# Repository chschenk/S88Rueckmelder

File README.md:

# S88Rueckmelder
S88 Rückmelder Modul zum Anschluss von Rückmeldern an eine S88N Zentrale

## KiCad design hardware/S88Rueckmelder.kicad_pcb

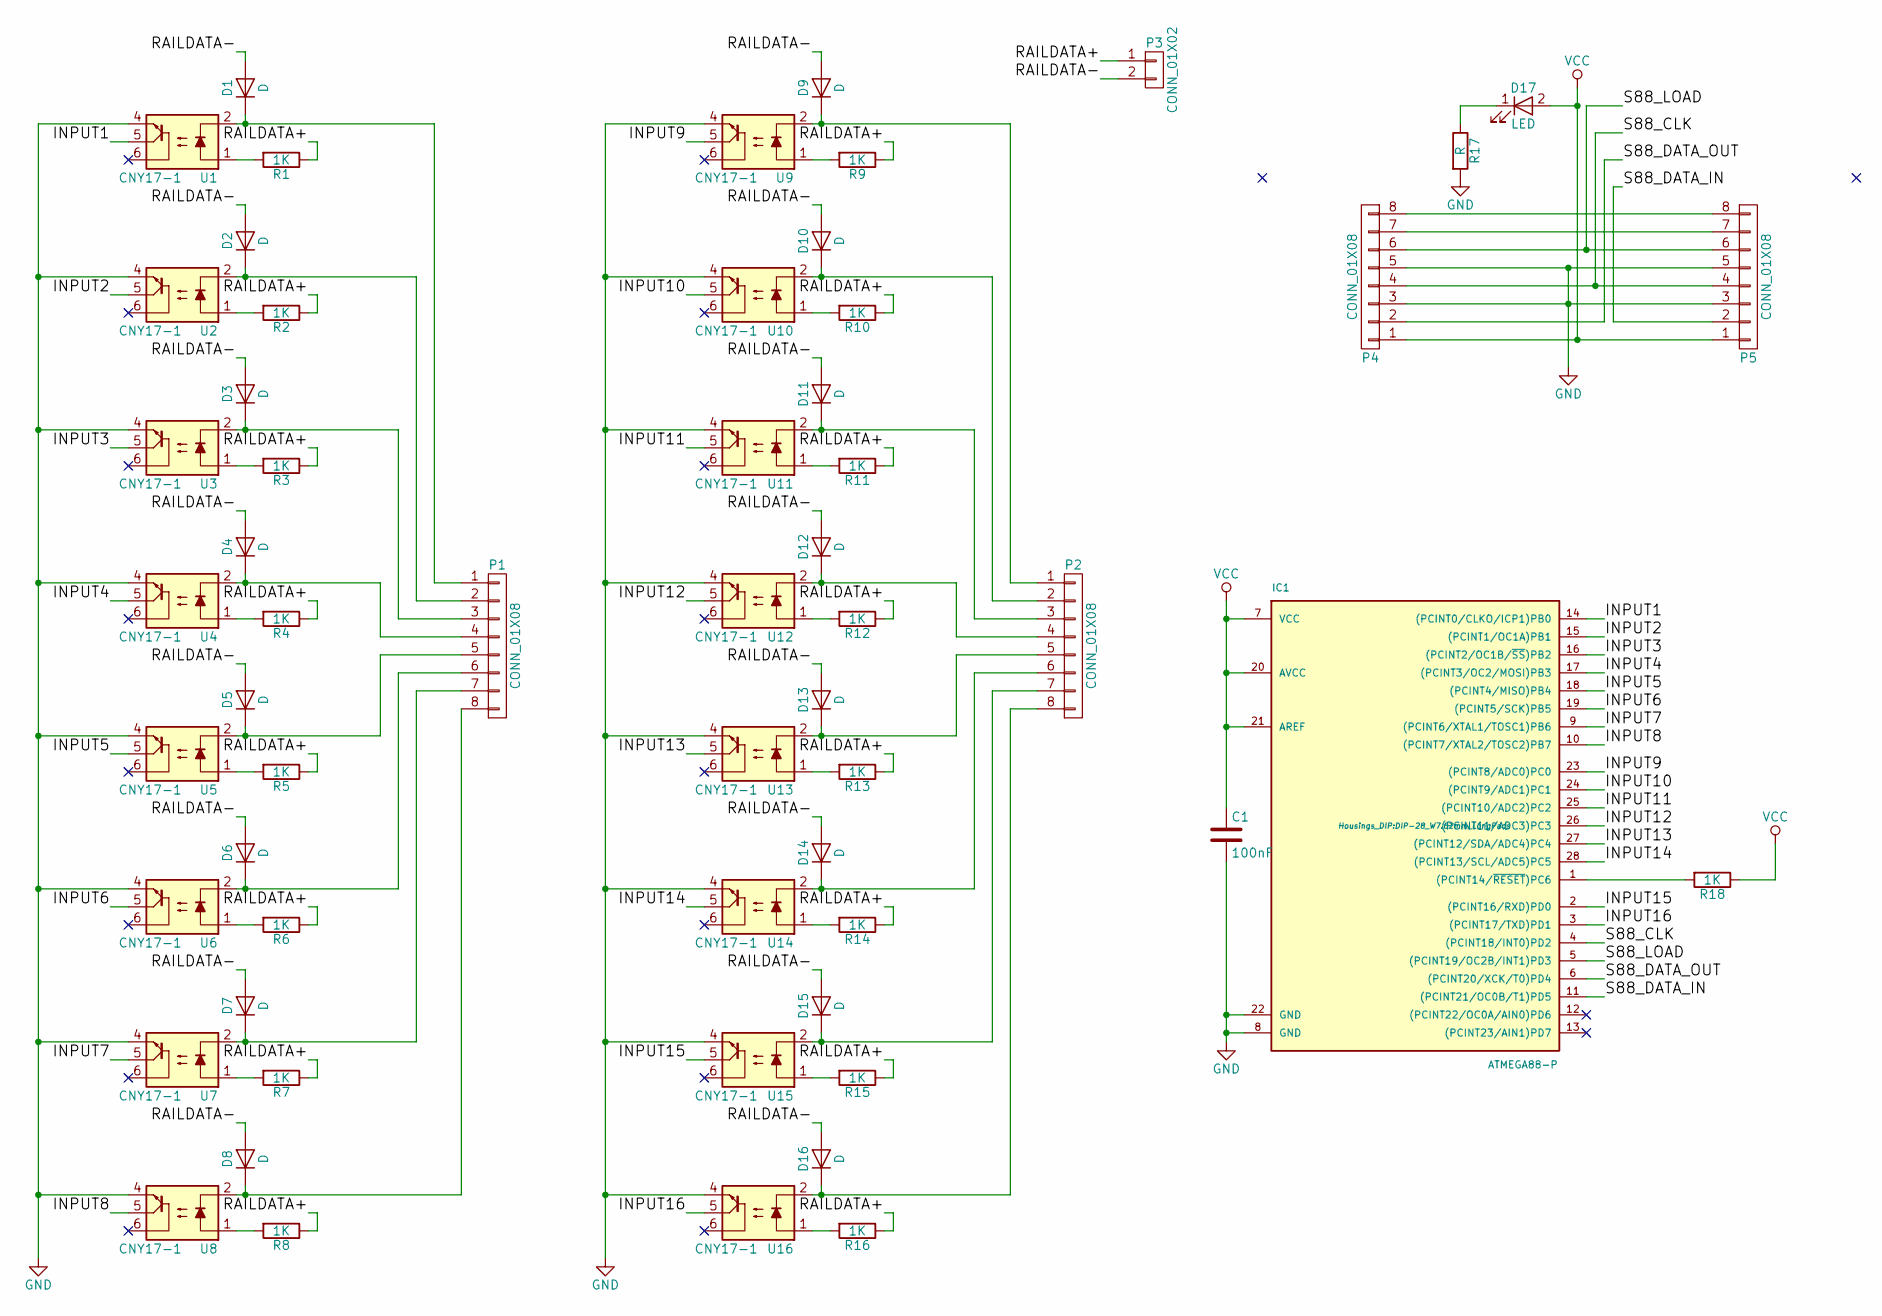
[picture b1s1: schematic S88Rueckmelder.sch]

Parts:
C1: 100nF; C_Disc_D5.1mm_W3.2mm_P5.00mm
D1, D2, D3, D4, D5, D6, D7, D8, D9, D10, D11, D12, D13, D14, D15, D16: D; D_DO-35_SOD27_P7.62mm_Horizontal
D17: LED; LED_D5.0mm
IC1: ATMEGA88-P; DIP-28_W7.62mm_LongPads
P1, P2: CONN_01X08; TerminalBlock_Phoenix_MKDS1.5-8pol
P3: CONN_01X02; AK300-2
P4, P5: CONN_01X08; RJ45_8
R1, R2, R3, R4, R5, R6, R7, R8, R9, R10, R11, R12, R13, R14, R15, R16: 1K; R_Axial_DIN0207_L6.3mm_D2.5mm_P7.62mm_Horizontal
R17: R; R_Axial_DIN0207_L6.3mm_D2.5mm_P10.16mm_Horizontal
R18: 1K; R_Axial_DIN0207_L6.3mm_D2.5mm_P10.16mm_Horizontal
U1, U2, U3, U4, U5, U6, U7, U8, U9, U10, U11, U12, U13, U14, U15, U16: CNY17-1; DIP-6_W7.62mm_LongPads

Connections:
/INPUT1: IC1.14 ((PCINT0/CLKO/ICP1)PB0), U1.5
/INPUT2: IC1.15 ((PCINT1/OC1A)PB1), U2.5
/INPUT3: IC1.16 ((PCINT2/OC1B/~SS~)PB2), U3.5
/INPUT4: IC1.17 ((PCINT3/OC2/MOSI)PB3), U4.5
/INPUT5: IC1.18 ((PCINT4/MISO)PB4), U5.5
/INPUT6: IC1.19 ((PCINT5/SCK)PB5), U6.5
/INPUT7: IC1.9 ((PCINT6/XTAL1/TOSC1)PB6), U7.5
/INPUT8: IC1.10 ((PCINT7/XTAL2/TOSC2)PB7), U8.5
/INPUT9: IC1.23 ((PCINT8/ADC0)PC0), U9.5
/INPUT10: IC1.24 ((PCINT9/ADC1)PC1), U10.5
/INPUT11: IC1.25 ((PCINT10/ADC2)PC2), U11.5
/INPUT12: IC1.26 ((PCINT11/ADC3)PC3), U12.5
/INPUT13: IC1.27 ((PCINT12/SDA/ADC4)PC4), U13.5
/INPUT14: IC1.28 ((PCINT13/SCL/ADC5)PC5), U14.5
/INPUT15: IC1.2 ((PCINT16/RXD)PD0), U15.5
/INPUT16: IC1.3 ((PCINT17/TXD)PD1), U16.5
/RAILDATA+: P3.1, R1.1, R2.1, R3.1, R4.1, R5.1, R6.1, R7.1, R8.1, R9.1, R10.1, R11.1, R12.1, R13.1, R14.1, R15.1, R16.1
/RAILDATA-: D1.2 (A), D2.2 (A), D3.2 (A), D4.2 (A), D5.2 (A), D6.2 (A), D7.2 (A), D8.2 (A), D9.2 (A), D10.2 (A), D11.2 (A), D12.2 (A), D13.2 (A), D14.2 (A), D15.2 (A), D16.2 (A), P3.2
/S88_CLK: IC1.4 ((PCINT18/INT0)PD2), P4.4, P5.4
/S88_DATA_IN: IC1.11 ((PCINT21/OC0B/T1)PD5), P5.2
/S88_DATA_OUT: IC1.6 ((PCINT20/XCK/T0)PD4), P4.2
/S88_LOAD: IC1.5 ((PCINT19/OC2B/INT1)PD3), P4.6, P5.6
GND: C1.2, IC1.8 (GND), IC1.22 (GND), P4.3, P4.5, P5.3, P5.5, R17.2, U1.4, U2.4, U3.4, U4.4, U5.4, U6.4, U7.4, U8.4, U9.4, U10.4, U11.4, U12.4, U13.4, U14.4, U15.4, U16.4
unnamed: D1.1 (K), P1.1, U1.2
unnamed: D2.1 (K), P1.2, U2.2
unnamed: D3.1 (K), P1.3, U3.2
unnamed: D4.1 (K), P1.4, U4.2
unnamed: D5.1 (K), P1.5, U5.2
unnamed: D6.1 (K), P1.6, U6.2
unnamed: D7.1 (K), P1.7, U7.2
unnamed: D8.1 (K), P1.8, U8.2
unnamed: D9.1 (K), P2.1, U9.2
unnamed: D10.1 (K), P2.2, U10.2
unnamed: D11.1 (K), P2.3, U11.2
unnamed: D12.1 (K), P2.4, U12.2
unnamed: D13.1 (K), P2.5, U13.2
unnamed: D14.1 (K), P2.6, U14.2
unnamed: D15.1 (K), P2.7, U15.2
unnamed: D16.1 (K), P2.8, U16.2
unnamed: D17.1 (K), R17.1
unnamed: IC1.1 ((PCINT14/~RESET~)PC6), R18.2
unnamed: P4.7, P5.7
unnamed: P4.8, P5.8
unnamed: R1.2, U1.1
unnamed: R2.2, U2.1
unnamed: R3.2, U3.1
unnamed: R4.2, U4.1
unnamed: R5.2, U5.1
unnamed: R6.2, U6.1
unnamed: R7.2, U7.1
unnamed: R8.2, U8.1
unnamed: R9.2, U9.1
unnamed: R10.2, U10.1
unnamed: R11.2, U11.1
unnamed: R12.2, U12.1
unnamed: R13.2, U13.1
unnamed: R14.2, U14.1
unnamed: R15.2, U15.1
unnamed: R16.2, U16.1
VCC: C1.1, D17.2 (A), IC1.7 (VCC), IC1.20 (AVCC), IC1.21 (AREF), P4.1, P5.1, R18.1

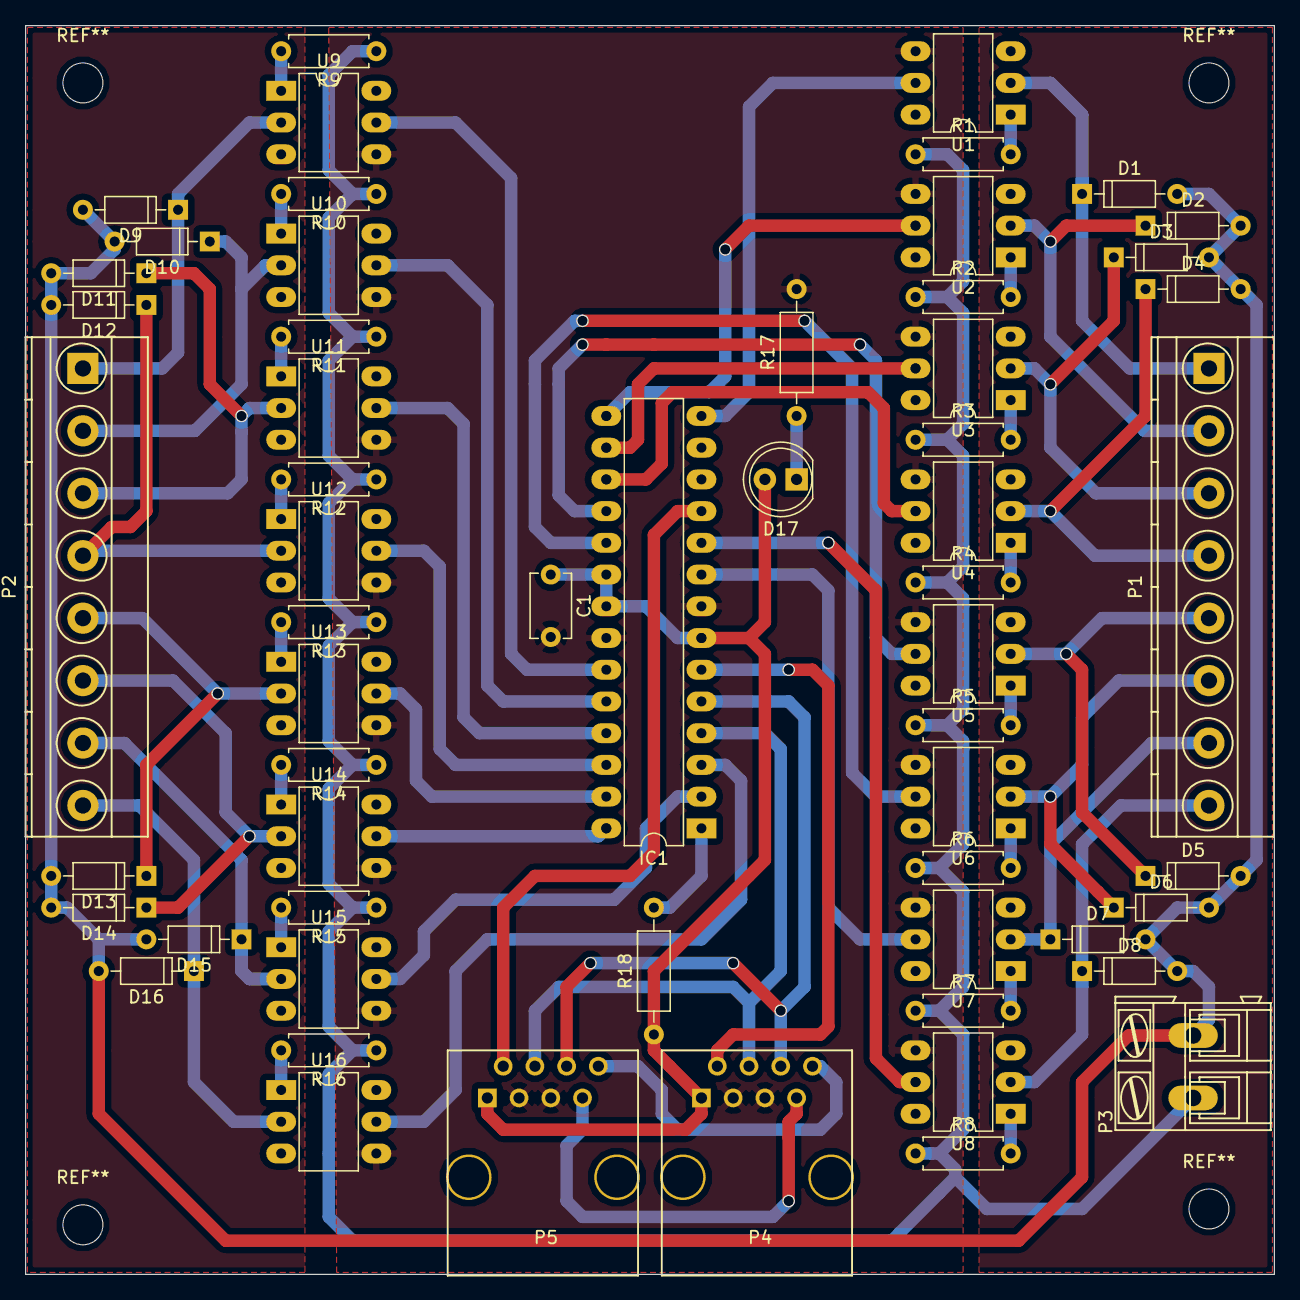
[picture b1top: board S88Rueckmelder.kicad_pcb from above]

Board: 2 copper layers, 100.0 x 100.0 mm, 58 parts (0 on the bottom side), 60 nets.

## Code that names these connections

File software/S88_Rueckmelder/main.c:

/*
 * S88_Rueckmelder.c
 *
 * Created: 15.12.2017 21:37:57
 * Author : Christopher
 */ 

#include <avr/io.h>
#include <avr/interrupt.h>

static uint16_t values;
static uint16_t loaded_values;
ISR(INT0_vect) //CLK
{
	cli();
	if(loaded_values & 0x01)
	{
		PORTD |= (1 << PD4);
	}else{
		PORTD &= ~(1 << PD4);
	}
	loaded_values = loaded_values >> 1;
	if(PIND & (1 << PD5))
	{
		loaded_values |= 0x8000;
	}else{
		loaded_values &= ~(0x8000);
	}
	sei();
}

ISR(INT1_vect) //LOAD
{
	cli();
	loaded_values = values;
	values = 0;
	sei();
}

void init()
{
	DDRB = 0x00;
	PORTB = 0xff;
	DDRC = 0x00;
	PORTC = 0xff;
	DDRD = (1 << DDD4);
	PORTD = ~(1 << PD4);
	MCUCR = (1 << ISC11) | (1 << ISC10) | (1 << ISC01) | (1 << ISC00);
	GICR = (1 << INT0) | (1 << INT1);
	
	sei();
}

int main(void)
{
	init();
	while (1)
	{
		uint16_t upper = 0;
		if(PIND & (1 << PD1))
		{
			upper |= 0x80;
		}
		if(PIND & (1 << PD0))
		{
			upper |= 0x40;
		}
		upper |= (PINC & 0x3f);//0x3f (0x3d)
		upper = upper << 8;
		values |= ~(PINB | upper);
	}
}

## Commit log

2017-12-24 Fixed Typo
2017-12-24 Inital commit
